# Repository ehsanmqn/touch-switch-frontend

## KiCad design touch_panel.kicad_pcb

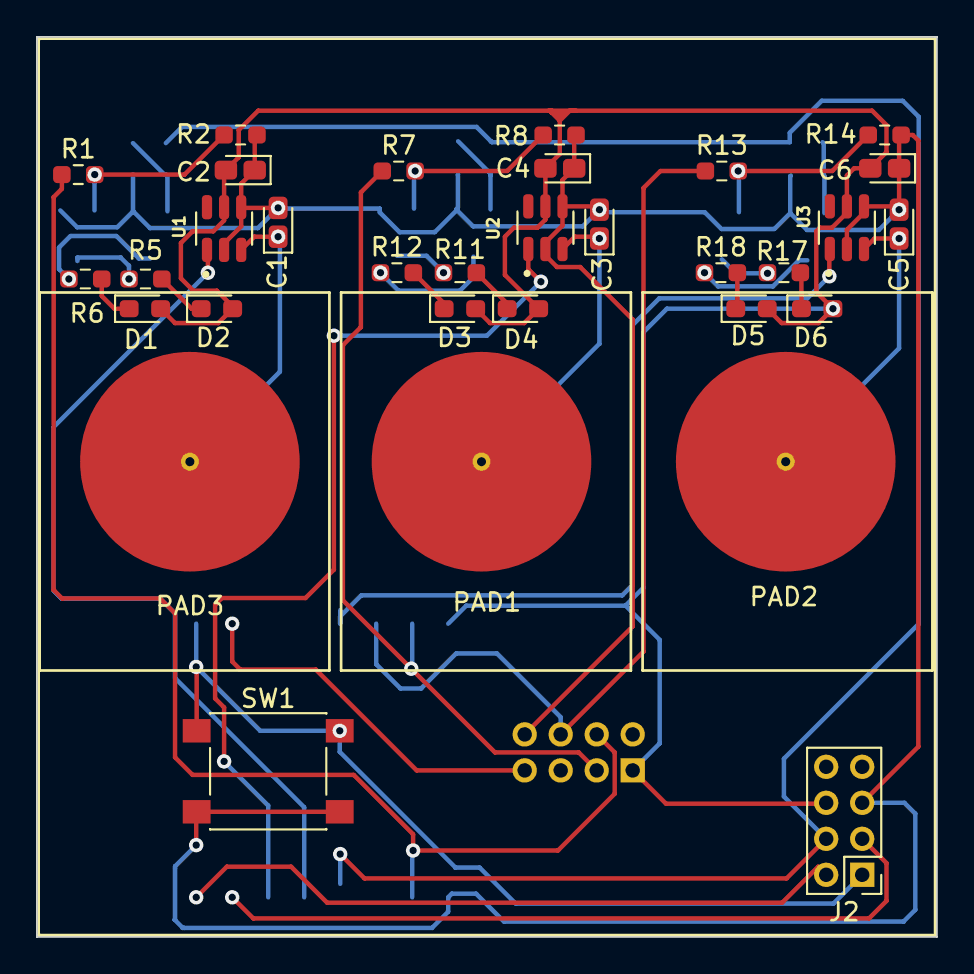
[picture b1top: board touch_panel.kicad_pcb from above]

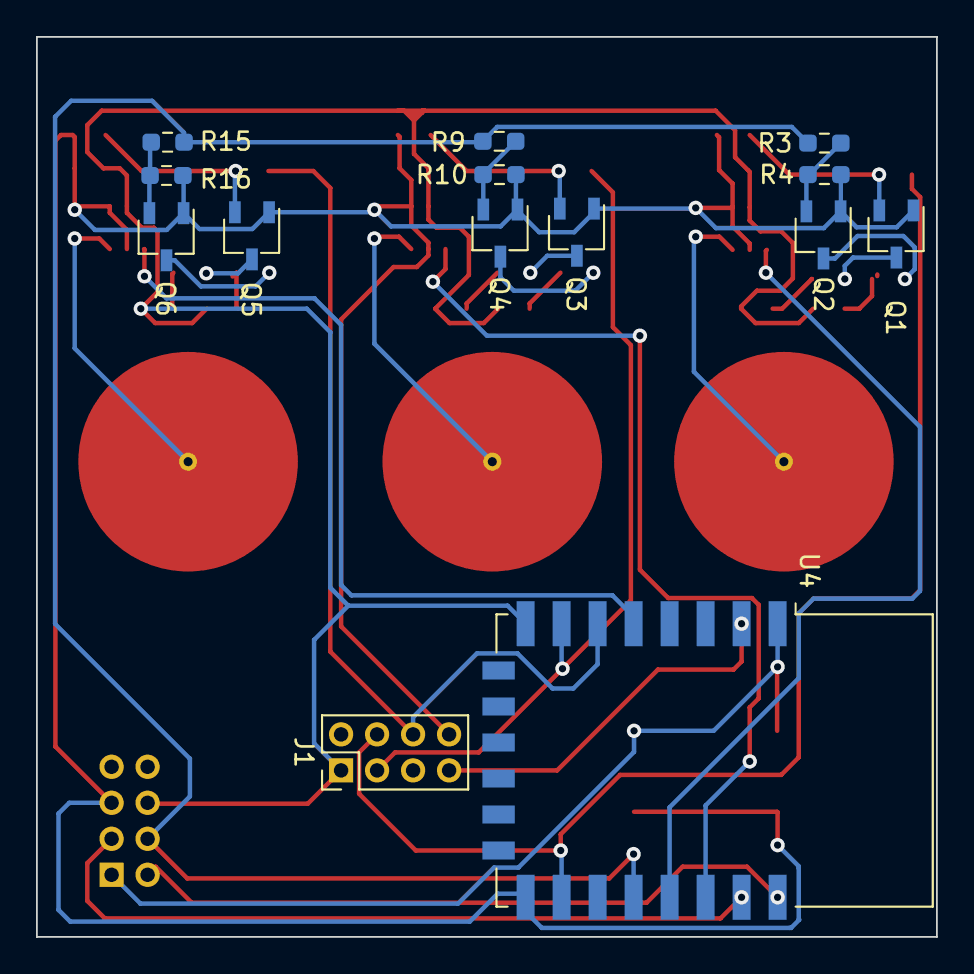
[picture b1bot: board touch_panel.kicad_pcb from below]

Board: 2 copper layers, 50.0 x 50.0 mm, 46 parts (14 on the bottom side), 34 nets.

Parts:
C1, C3, C5: 0-50 pF (30 pF); CP_EIA-1608-10_AVX-L_Pad1.25x1.05mm_HandSolder
C2, C4, C6: 100nF; CP_EIA-1608-10_AVX-L_Pad1.25x1.05mm_HandSolder
D1, D3, D5: BLUE; LED_0603_1608Metric_Pad1.05x0.95mm_HandSolder
D2, D4, D6: WHITE; LED_0603_1608Metric_Pad1.05x0.95mm_HandSolder
J1: 2x4 SMD 2.0 MM; PinHeader_2x04_P2.00mm_Vertical
J2: 2x4 Regular; PinHeader_2x04_P2.00mm_Vertical
PAD1: Sense pad 1; senspad
PAD2: Sense pad 2; senspad
PAD3: Sense pad 3; senspad
Q1, Q2, Q3, Q4, Q5, Q6: MMBT2222; TSOT-23
R1, R3, R7, R9, R13, R15: 1K; R_0603_1608Metric_Pad0.98x0.95mm_HandSolder
R2, R4, R8, R10, R14, R16: 10K; R_0603_1608Metric_Pad0.98x0.95mm_HandSolder
R5, R6, R11, R12, R17, R18: 10R; R_0603_1608Metric_Pad0.98x0.95mm_HandSolder
SW1: Reset Switch; SW_Push_1P1T_NO_6x6mm_H9.5mm
U1: TTP223_1; SOT95P285X126-6N
U2: TTP223_2; SOT95P285X126-6N
U3: TTP223_3; SOT95P285X126-6N
U4: ESP-12E

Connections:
+3V3: C2.2, C4.2, C6.2, D1.2 (A), D2.2 (A), D3.2 (A), D4.2 (A), D5.2 (A), D6.2 (A), J1.1, J2.6, U1.5 (VDD), U2.5 (VDD), U3.5 (VDD), U4.3 (EN), U4.8 (VCC)
BLUELED: J2.4, R3.1, R9.1, R15.1, U4.18 (GPIO0)
GND: C1.2, C2.1, C3.2, C4.1, C5.2, C6.1, J1.8, J2.5, Q1.1 (E), Q2.1 (E), Q3.1 (E), Q4.1 (E), Q5.1 (E), Q6.1 (E), R2.1, R4.1, R8.1, R10.1, R14.1, R16.1, SW1.2, U1.2 (VSS), U1.4 (VSS), U2.2 (VSS), U2.4 (VSS), U3.2 (VSS), U3.4 (VSS), U4.15 (GND)
unnamed: C1.1, PAD3.6, U1.3 (I)
unnamed: C3.1, PAD1.6, U2.3 (I)
unnamed: C5.1, PAD2.6, U3.3 (I)
unnamed: D1.1 (K), R6.2
unnamed: D2.1 (K), R5.2
unnamed: D3.1 (K), R12.2
unnamed: D4.1 (K), R11.2
unnamed: D5.1 (K), R18.2
unnamed: D6.1 (K), R17.2
unnamed: Q1.2 (B), R1.2, R2.2
unnamed: Q1.3 (C), R5.1
unnamed: Q2.2 (B), R3.2, R4.2
unnamed: Q2.3 (C), R6.1
unnamed: Q3.2 (B), R7.2, R8.2
unnamed: Q3.3 (C), R11.1
unnamed: Q4.2 (B), R9.2, R10.2
unnamed: Q4.3 (C), R12.1
unnamed: Q5.2 (B), R13.2, R14.2
unnamed: Q5.3 (C), R17.1
unnamed: Q6.2 (B), R15.2, R16.2
unnamed: Q6.3 (C), R18.1
RST: J2.1, SW1.1, U4.1 (~RST)
RX: J2.3, U4.21 (GPIO3/RXD)
Relay 1: J1.4, R1.1, U4.16 (GPIO15)
Relay 2: J1.3, R7.1, U4.7 (GPIO13)
Relay 3: J1.6, R13.1, U4.6 (GPIO12)
TEMP: J1.7, U4.2 (ADC)
TX: J2.2, U4.22 (GPIO1/TXD)
Touch 1: U1.1 (Q), U4.19 (GPIO4)
Touch 2: U2.1 (Q), U4.20 (GPIO5)
Touch 3: U3.1 (Q), U4.5 (GPIO14)

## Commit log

2022-03-13 Some changes performed
2022-03-14 Minor modification added
2022-03-19 Finalized for printing
2022-04-03 Some routes updated for better cut
